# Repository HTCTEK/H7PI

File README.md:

# H7PI

## 量产版本历史
[v0.2](https://gitee.com/htctek/H7PI/tree/bf5159e9c3666d05ed6d5055ce2db61eb0288070) 特点：带8bits LCD接口    
[v1.0](https://gitee.com/htctek/H7PI/tree/e8b1aa18095ffa30b805f85c88335dfa602a2d0a) 特点：除了SD卡座，QSPI Flash引脚，SPI flash/psram引脚外，引出所有引脚，使用type-c接口，取消8bits LCD接口。

## 使用说明 / User Manual
中文：[使用说明](https://pinno.cc)

## 获取一个H7PI / Buy One
淘宝：[购买链接 / shop](https://item.taobao.com/item.htm?spm=a230r.1.14.18.71f35247DnH8yH&id=606908438435&ns=1&abbucket=14#detail)

## Platform
* [H7PI_Arduino](https://github.com/htctek/H7PI_Arduino) is for users who are used to develop arduino
* [H7PI_Samples](https://github.com/htctek/H7PI_Samples) is for users who are used to develop with MDK Keil, but also give an entry for arduino and support freeRTOS.

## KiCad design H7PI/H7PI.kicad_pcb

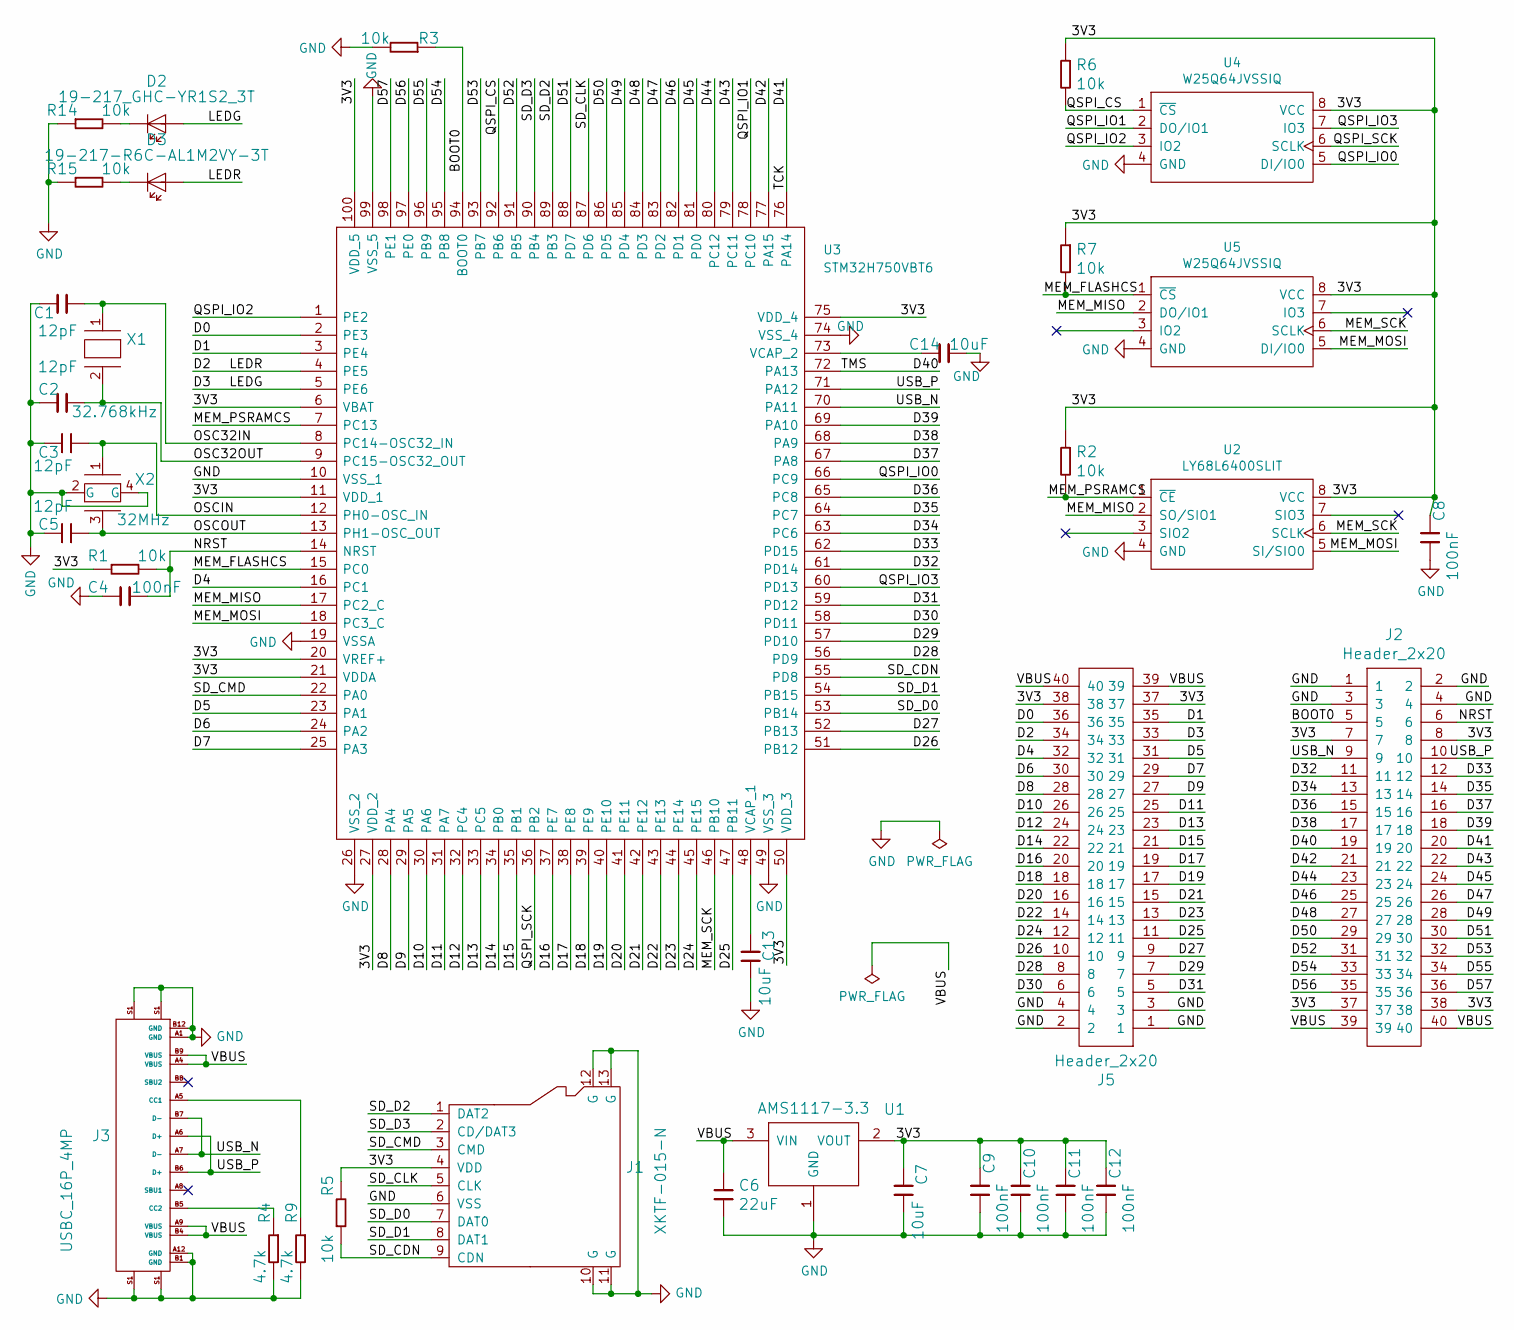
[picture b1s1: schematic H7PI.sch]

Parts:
C1, C2, C3, C5: 12pF; C_0402_1005Metric; PartNumber 0402CG120J500NT
C4, C8, C9, C10, C11, C12: 100nF; C_0402_1005Metric; PartNumber 0402B104K500NT
C6: 22uF; C_0805_2012Metric; PartNumber CL21A226MAQNNNE
C7, C13, C14: 10uF; C_0402_1005Metric; PartNumber 0402X106M6R3NT
D2: 19-217_GHC-YR1S2_3T; LED_0603_1608Metric; PartNumber 19-217/GHC-YR1S2/3T
D3: 19-217-R6C-AL1M2VY-3T; LED_0603_1608Metric; PartNumber 19-217/R6C-AL1M2VY/3T
J1: XKTF-015-N; Connector_MicroSD_TF_XKB_XKTF-015-N_14.75x17.5mm; PartNumber XKTF-015-N
J2, J5: Header_2x20; PinHeader_2x20_P2.54mm_Vertical
J3: USBC_16P_4MP; USB_C_Receptacle_Palconn_UTC16-G; PartNumber TYPE C连接器USB3.1系列母座端单排16P贴板有柱-5A大电流新ES
R1, R2, R3, R5, R6, R7, R14, R15: 10k; R_0402_1005Metric; PartNumber 0402WGF1002TCE
R4, R9: 4.7k; R_0402_1005Metric; PartNumber 0402WGF4701TCE
U1: AMS1117-3.3; SOT-223; PartNumber AMS1117-3.3
U2: LY68L6400SLIT; SOIC-8_3.9x4.9mm_P1.27mm; PartNumber LY68L6400SLIT
U3: STM32H750VBT6; LQFP-100_14x14mm_P0.5mm; PartNumber STM32H750VBT6
U4, U5: W25Q64JVSSIQ; SOIC-8_5.23x5.23mm_P1.27mm; PartNumber W25Q64JVSSIQ
X1: 32.768kHz; Crystal_SMD_EuroQuartz_EQ161-2Pin_3.2x1.5mm; PartNumber SMD31327681252090
X2: 32MHz; Crystal_SMD_2520-4Pin_2.5x2.0mm; PartNumber S2232000082060

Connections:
/3V3: C7.1, C8.2, C9.2, C10.2, C11.2, C12.2, J1.4 (VDD), J2.7, J2.8, J2.37, J2.38, J5.37, J5.38, R1.1, R2.1, R5.2, R6.1, R7.1, U1.2 (VOUT), U2.8 (VCC), U3.6 (VBAT), U3.11 (VDD_1), U3.20 (VREF+), U3.21 (VDDA), U3.27 (VDD_2), U3.50 (VDD_3), U3.75 (VDD_4), U3.100 (VDD_5), U4.8 (VCC), U5.8 (VCC)
/BOOT0: J2.5, R3.1, U3.94 (BOOT0)
/D0: J5.36, U3.2 (PE3)
/D1: J5.35, U3.3 (PE4)
/D2: D3.2, J5.34, U3.4 (PE5)
/D3: D2.2, J5.33, U3.5 (PE6)
/D4: J5.32, U3.16 (PC1)
/D5: J5.31, U3.23 (PA1)
/D6: J5.30, U3.24 (PA2)
/D7: J5.29, U3.25 (PA3)
/D8: J5.28, U3.28 (PA4)
/D9: J5.27, U3.29 (PA5)
/D10: J5.26, U3.30 (PA6)
/D11: J5.25, U3.31 (PA7)
/D12: J5.24, U3.32 (PC4)
/D13: J5.23, U3.33 (PC5)
/D14: J5.22, U3.34 (PB0)
/D15: J5.21, U3.35 (PB1)
/D16: J5.20, U3.37 (PE7)
/D17: J5.19, U3.38 (PE8)
/D18: J5.18, U3.39 (PE9)
/D19: J5.17, U3.40 (PE10)
/D20: J5.16, U3.41 (PE11)
/D21: J5.15, U3.42 (PE12)
/D22: J5.14, U3.43 (PE13)
/D23: J5.13, U3.44 (PE14)
/D24: J5.12, U3.45 (PE15)
/D25: J5.11, U3.47 (PB11)
/D26: J5.10, U3.51 (PB12)
/D27: J5.9, U3.52 (PB13)
/D28: J5.8, U3.56 (PD9)
/D29: J5.7, U3.57 (PD10)
/D30: J5.6, U3.58 (PD11)
/D31: J5.5, U3.59 (PD12)
/D32: J2.11, U3.61 (PD14)
/D33: J2.12, U3.62 (PD15)
/D34: J2.13, U3.63 (PC6)
/D35: J2.14, U3.64 (PC7)
/D36: J2.15, U3.65 (PC8)
/D37: J2.16, U3.67 (PA8)
/D38: J2.17, U3.68 (PA9)
/D39: J2.18, U3.69 (PA10)
/D40: J2.19, U3.72 (PA13)
/D41: J2.20, U3.76 (PA14)
/D42: J2.21, U3.77 (PA15)
/D43: J2.22, U3.79 (PC11)
/D44: J2.23, U3.80 (PC12)
/D45: J2.24, U3.81 (PD0)
/D46: J2.25, U3.82 (PD1)
/D47: J2.26, U3.83 (PD2)
/D48: J2.27, U3.84 (PD3)
/D49: J2.28, U3.85 (PD4)
/D50: J2.29, U3.86 (PD5)
/D51: J2.30, U3.88 (PD7)
/D52: J2.31, U3.91 (PB5)
/D53: J2.32, U3.93 (PB7)
/D54: J2.33, U3.95 (PB8)
/D55: J2.34, U3.96 (PB9)
/D56: J2.35, U3.97 (PE0)
/D57: J2.36, U3.98 (PE1)
/MEM_FLASHCS: R7.2, U3.15 (PC0), U5.1 (~CS)
/MEM_MISO: U2.2 (SO/SIO1), U3.17 (PC2_C), U5.2 (DO/IO1)
/MEM_MOSI: U2.5 (SI/SIO0), U3.18 (PC3_C), U5.5 (DI/IO0)
/MEM_PSRAMCS: R2.2, U2.1 (~CE), U3.7 (PC13)
/MEM_SCK: U2.6 (SCLK), U3.46 (PB10), U5.6 (SCLK)
/NRST: C4.1, J2.6, R1.2, U3.14 (NRST)
/OSC32IN: C1.2, U3.8 (PC14-OSC32_IN), X1.1
/OSC32OUT: C2.2, U3.9 (PC15-OSC32_OUT), X1.2
/OSCIN: C3.2, U3.12 (PH0-OSC_IN), X2.1
/OSCOUT: C5.2, U3.13 (PH1-OSC_OUT), X2.3
/QSPI_CS: R6.2, U3.92 (PB6), U4.1 (~CS)
/QSPI_IO0: U3.66 (PC9), U4.5 (DI/IO0)
/QSPI_IO1: U3.78 (PC10), U4.2 (DO/IO1)
/QSPI_IO2: U3.1 (PE2), U4.3 (IO2)
/QSPI_IO3: U3.60 (PD13), U4.7 (IO3)
/QSPI_SCK: U3.36 (PB2), U4.6 (SCLK)
/SD_CDN: J1.9 (CDN), R5.1, U3.55 (PD8)
/SD_CLK: J1.5 (CLK), U3.87 (PD6)
/SD_CMD: J1.3 (CMD), U3.22 (PA0)
/SD_D0: J1.7 (DAT0), U3.53 (PB14)
/SD_D1: J1.8 (DAT1), U3.54 (PB15)
/SD_D2: J1.1 (DAT2), U3.89 (PB3)
/SD_D3: J1.2 (CD/DAT3), U3.90 (PB4)
/USB_N: J2.9, J3.A7 (D-), J3.B7 (D-), U3.70 (PA11)
/USB_P: J2.10, J3.A6 (D+), J3.B6 (D+), U3.71 (PA12)
/VBUS: C6.1, J2.39, J2.40, J3.A4 (VBUS), J3.A9 (VBUS), J3.B4 (VBUS), J3.B9 (VBUS), J5.39, J5.40, U1.3 (VIN)
GND: C1.1, C2.1, C3.1, C4.2, C5.1, C6.2, C7.2, C8.1, C9.1, C10.1, C11.1, C12.1, C13.2, C14.2, J1.6 (VSS), J1.10 (G), J1.11 (G), J1.12 (G), J1.13 (G), J2.1, J2.2, J2.3, J2.4, J3.A1 (GND), J3.A12 (GND), J3.B1 (GND), J3.B12 (GND), J3.S1, J5.1, J5.2, J5.3, J5.4, R3.2, R4.2, R9.2, R14.1, R15.1, U1.1 (GND), U2.4 (GND), U3.10 (VSS_1), U3.19 (VSSA), U3.26 (VSS_2), U3.49 (VSS_3), U3.74 (VSS_4), U3.99 (VSS_5), U4.4 (GND), U5.4 (GND), X2.2 (G), X2.4 (G)
unnamed: C13.1, U3.48 (VCAP_1)
unnamed: C14.1, U3.73 (VCAP_2)
unnamed: D2.1, R14.2
unnamed: D3.1, R15.2
unnamed: J3.A5 (CC1), R9.1
unnamed: J3.B5 (CC2), R4.1

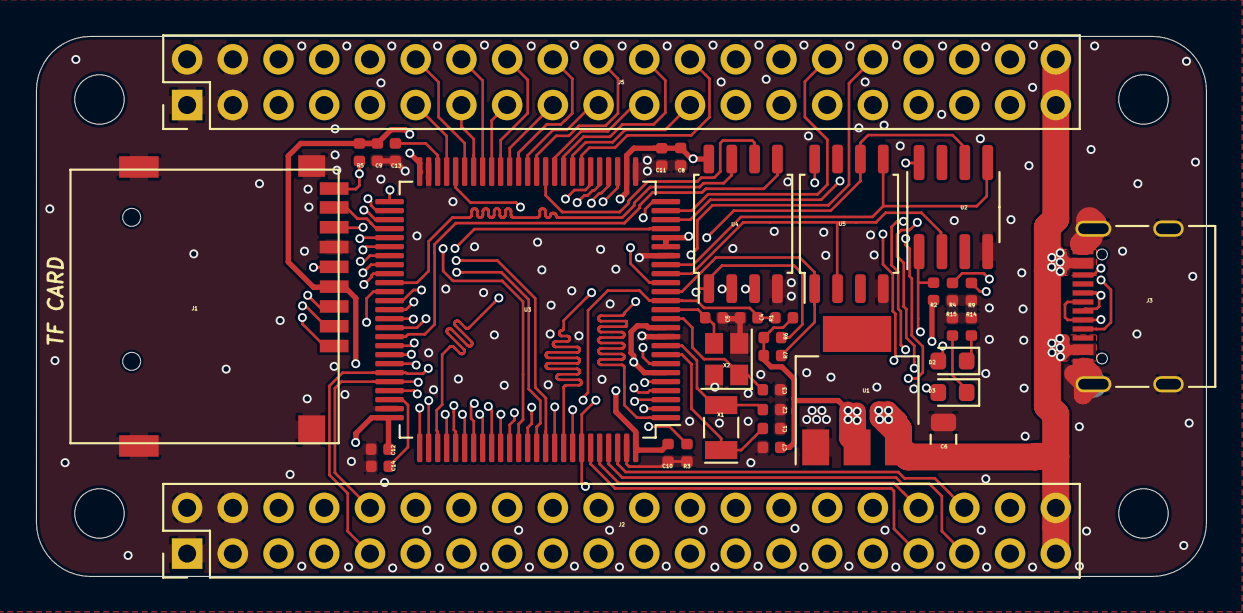
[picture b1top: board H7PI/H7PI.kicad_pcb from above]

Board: 4 copper layers, 65.0 x 30.0 mm, 37 parts (0 on the bottom side), 93 nets.

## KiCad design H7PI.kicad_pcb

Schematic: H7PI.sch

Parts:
C4, C8, C11, C12, C15, C16, C17, C18: 100nF; C_0402_1005Metric; PartNumber 0402B104K500NT
C5, C9: 1uF; C_0603_1608Metric; PartNumber 0603B105K500NT
C10: 100uF/10V; C_1210_3225Metric; PartNumber CL32A107MPVNNNE
C13, C14: 10uF; C_0402_1005Metric; PartNumber 0402X106M6R3NT
D1: 1N5819WS; D_SOD-323; PartNumber 1N5819WS
D2: 19-217_GHC-YR1S2_3T; LED_0603_1608Metric; PartNumber 19-217/GHC-YR1S2/3T
D3: 19-217-R6C-AL1M2VY-3T; LED_0603_1608Metric; PartNumber 19-217/R6C-AL1M2VY/3T
F1, F2: 0458002.DR; Fuse_1206_3216Metric; PartNumber 0458002.DR
J1: XKTF-015-N; Connector_MicroSD_TF_XKB_XKTF-015-N_14.75x17.5mm; PartNumber XKTF-015-N
J2: Header_2x10; PinHeader_2x10_P2.54mm_Vertical
J3, J6: microUSB; USB_Micro-B_Molex-105017-0001; PartNumber micro USB母座
J4: AFC07-S24ECA-00; Connector_FPC_JS_AFC07-S24ECA-00_1x24-1MP_P0.5mm_UpSideCont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; PartNumber AFC07-S24ECA-00
J5: Header_2x20; PinHeader_2x20_P2.54mm_Vertical
J7: Header_1x2; PinHeader_1x02_P1.27mm_Vertical
J8, J9: Header_1x1; TestPoint_Pad_D1.0mm
L1: CIGT201610LH2R2MNE; L_0805_2012Metric_Pad1.15x1.40mm_HandSolder; PartNumber CIGT201610LH2R2MNE
Q1: CJ2101; SOT-323_SC-70; PartNumber CJ2101
Q2: CJ2102; SOT-323_SC-70; PartNumber CJ2102
R1, R3, R5, R6, R7, R8, R9, R10, R13, R14, R15: 10k; R_0402_1005Metric; PartNumber 0402WGF1002TCE
R2: 33k; R_0402_1005Metric; PartNumber 0402WGF3302TCE
R4: 100k; R_0402_1005Metric; PartNumber 0402WGF1003TCE
R11: 4.7; R_0402_1005Metric; PartNumber 0402WGF470KTCE
R12: 1k; R_0402_1005Metric; PartNumber 0402WGF1001TCE
U2: MT1470; SOT-23-6; PartNumber MT1470
U3: STM32H750VBT6; LQFP-100_14x14mm_P0.5mm; PartNumber STM32H750VBT6
U4, U5: W25Q64JVSSIQ; SOIC-8_5.23x5.23mm_P1.27mm; PartNumber W25Q64JVSSIQ

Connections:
/3V3: C12.2, C15.2, C16.2, F1.2, J1.4 (VDD), J2.1, J4.1, J5.1, J5.17, Q1.2, R1.1, R5.2, R6.1, R7.1, R8.1, R9.1, R10.1, U3.6 (VBAT), U3.11 (VDD_1), U3.20 (VREF+), U3.21 (VDDA), U3.27 (VDD_2), U3.50 (VDD_3), U3.75 (VDD_4), U3.100 (VDD_5), U4.8 (VCC), U5.8 (VCC)
/BUZZER: R12.1, U3.59 (PD12)
/FLASH_CS: R7.2, U3.51 (PB12), U5.1 (~CS)
/FLASH_MISO: U3.17 (PC2_C), U5.2 (DO/IO1)
/FLASH_MOSI: U3.18 (PC3_C), U5.5 (DI/IO0)
/FLASH_SCK: U3.52 (PB13), U5.6 (SCLK)
/IO1: J2.3, U3.57 (PD10)
/IO2: J2.5, U3.60 (PD13)
/IO3: J2.7, U3.67 (PA8)
/IO4: J2.9, U3.72 (PA13)
/IO5: J2.11, U3.76 (PA14)
/IO6: J2.13, U3.77 (PA15)
/IO7: J2.15, U3.79 (PC11)
/IO8: J2.17, U3.80 (PC12)
/IO9: J2.18, U3.83 (PD2)
/IO10: J2.16, U3.84 (PD3)
/IO11: J2.14, U3.87 (PD6)
/IO12: J2.12, U3.88 (PD7)
/IO13: J2.10, U3.91 (PB5)
/IO14: J2.8, U3.96 (PB9)
/IO15: J2.6, U3.97 (PE0)
/IO16: J2.4, U3.98 (PE1)
/PI_CE0: J5.24, U3.41 (PE11)
/PI_CE1: J5.26, U3.45 (PE15)
/PI_GPIO0: J5.11, U3.2 (PE3)
/PI_GPIO1: J5.12, U3.3 (PE4)
/PI_GPIO2: J5.13, U3.4 (PE5)
/PI_GPIO3: J5.15, U3.5 (PE6)
/PI_GPIO4: J5.16, U3.7 (PC13)
/PI_GPIO5: J5.18, U3.15 (PC0)
/PI_GPIO6: J5.22, U3.24 (PA2)
/PI_GPIO7: J5.7, U3.25 (PA3)
/PI_GPIO21: J5.29, U3.28 (PA4)
/PI_GPIO22: J5.31, U3.29 (PA5)
/PI_GPIO23: J5.33, U3.30 (PA6)
/PI_GPIO24: J5.35, U3.31 (PA7)
/PI_GPIO25: J5.37, U3.32 (PC4)
/PI_GPIO26: J5.32, U3.33 (PC5)
/PI_GPIO27: J5.36, U3.34 (PB0)
/PI_GPIO28: J5.38, U3.35 (PB1)
/PI_GPIO29: J5.40, U3.56 (PD9)
/PI_MISO: J5.21, U3.43 (PE13)
/PI_MOSI: J5.19, U3.44 (PE14)
/PI_RXD: J5.10, U3.69 (PA10)
/PI_SCK: J5.23, U3.42 (PE12)
/PI_SCL0: J5.28, U3.95 (PB8)
/PI_SCL1: J5.5, U3.46 (PB10)
/PI_SDA0: J5.27, U3.93 (PB7)
/PI_SDA1: J5.3, U3.47 (PB11)
/PI_TXD: J5.8, U3.68 (PA9)
/QSPI_CS: R6.2, U3.92 (PB6), U4.1 (~CS)
/QSPI_IO0: U3.66 (PC9), U4.5 (DI/IO0)
/QSPI_IO1: U3.78 (PC10), U4.2 (DO/IO1)
/QSPI_IO2: U3.1 (PE2), U4.3 (IO2)
/QSPI_IO3: U3.23 (PA1), U4.7 (IO3)
/QSPI_SCK: U3.36 (PB2), U4.6 (SCLK)
/TFT_BL: Q1.1, R10.2, U3.63 (PC6)
/TFT_CS: J4.5, R9.2, U3.64 (PC7)
/TFT_DB8: J4.17, U3.61 (PD14)
/TFT_DB9: J4.18, U3.62 (PD15)
/TFT_DB10: J4.19, U3.81 (PD0)
/TFT_DB11: J4.20, U3.82 (PD1)
/TFT_DB12: J4.21, U3.37 (PE7)
/TFT_DB13: J4.22, U3.38 (PE8)
/TFT_DB14: J4.23, U3.39 (PE9)
/TFT_DB15: J4.24, U3.40 (PE10)
/TFT_RD: J4.8, U3.85 (PD4)
/TFT_RS: J4.6, U3.58 (PD11)
/TFT_RST: C17.2, J4.4, R8.2, U3.65 (PC8)
/TFT_WR: J4.7, U3.86 (PD5)
/TF_CDN: J1.9 (CDN), R5.1, U3.55 (PD8)
/TF_CLK: J1.5 (CLK), U3.16 (PC1)
/TF_CMD: J1.3 (CMD), U3.22 (PA0)
/TF_DATA0: J1.7 (DAT0), U3.53 (PB14)
/TF_DATA1: J1.8 (DAT1), U3.54 (PB15)
/TF_DATA2: J1.1 (DAT2), U3.89 (PB3)
/TF_DATA3: J1.2 (CD/DAT3), U3.90 (PB4)
/USB_N: J3.2, J6.2, U3.70 (PA11); also elsewhere on the board
/USB_P: J3.3, J6.3, U3.71 (PA12); also elsewhere on the board
/VBUS: C5.1, C8.2, D1.1, F2.1, J2.2, J5.2, J5.4, J7.1, U2.3; also elsewhere on the board
GND: C4.2, C5.2, C8.1, C10.2, C11.1, C12.1, C13.2, C14.2, C15.1, C16.1, C17.1, C18.2, J1.6 (VSS), J1.10 (G), J1.11 (G), J1.12 (G), J1.13 (G), J2.19, J2.20, J3.5, J3.6, J4.2, J4.9, J4.10, J4.11, J4.12, J4.13, J4.14, J4.15, J4.16, J4.MP, J5.6, J5.9, J5.14, J5.20, J5.25, J5.30, J5.34, J5.39, J6.5, J6.6, J8.1, J9.1, Q2.2, R2.2, R3.1, R13.2, R14.1, R15.1, U2.1, U3.10 (VSS_1), U3.19 (VSSA), U3.26 (VSS_2), U3.49 (VSS_3), U3.74 (VSS_4), U3.99 (VSS_5), U4.4 (GND), U5.4 (GND); also elsewhere on the board
unnamed: C4.1, R1.2, U3.14 (NRST)
unnamed: C9.1, U2.6
unnamed: C9.2, L1.1, U2.2
unnamed: C10.1, C11.2, F1.1, L1.2, R4.2
unnamed: C13.1, U3.48 (VCAP_1)
unnamed: C14.1, U3.73 (VCAP_2)
unnamed: C18.1, D1.2, J7.2, Q2.3
unnamed: D2.1, R14.2
unnamed: D2.2, U3.8 (PC14-OSC32_IN)
unnamed: D3.1, R15.2
unnamed: D3.2, U3.9 (PC15-OSC32_OUT)
unnamed: F2.2, J3.1, J6.1
unnamed: J4.3, R11.2
unnamed: Q1.3, R11.1
unnamed: Q2.1, R12.2, R13.1
unnamed: R2.1, R4.1, U2.4
unnamed: R3.2, U3.94 (BOOT0)
unnamed 98: U2.5; also elsewhere on the board

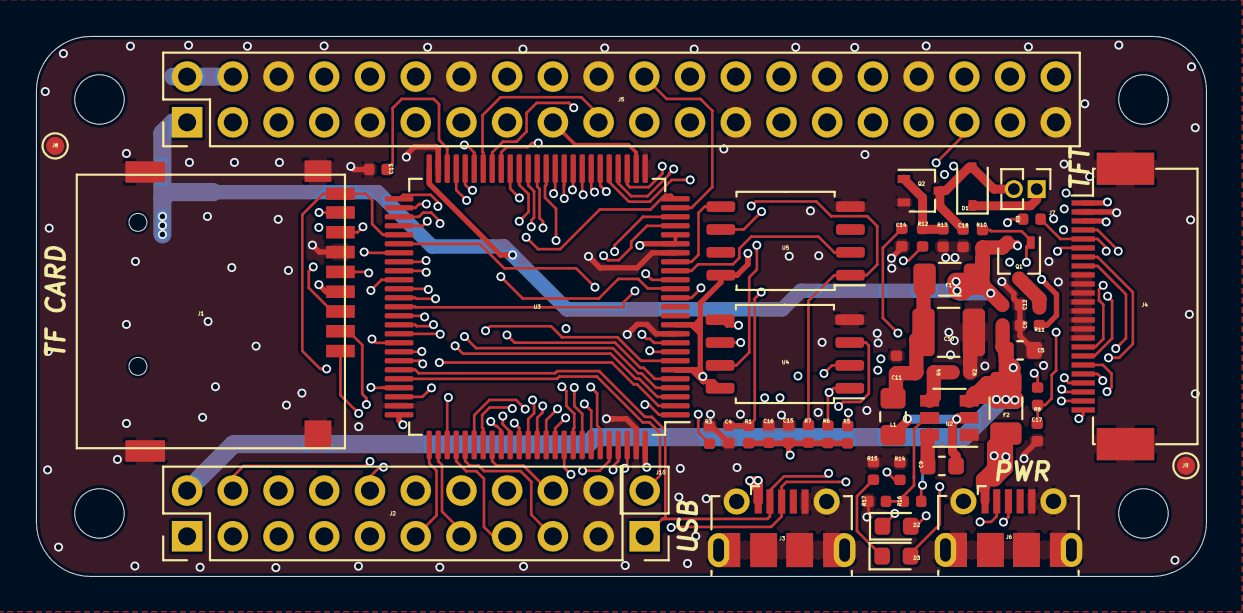
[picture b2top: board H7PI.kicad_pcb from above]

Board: 4 copper layers, 65.0 x 30.0 mm, 52 parts (0 on the bottom side), 99 nets.

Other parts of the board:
J10: DNP; PinHeader_1x02_P2.54mm_Vertical
R16: 100k; R_0402_1005Metric
R17: 33k; R_0402_1005Metric

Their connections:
/USB_N: J10.1; also elsewhere on the board
/USB_P: J10.2; also elsewhere on the board
/VBUS: R16.1; also elsewhere on the board
GND: R17.2; also elsewhere on the board
unnamed 98: R16.2, R17.1; also elsewhere on the board

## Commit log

2019-10-29 0.2版本，经试产可用于量产
2019-12-24 add README.md.
2019-12-24 更新了图纸的信息
2019-12-24 更新readme，增加中文简要说明
2019-12-24 增加英文首页readme add english readme
2019-12-28 v0.3 1. 增加电压支持到12V 2. 增加双USB口通信（不能同时用） 3. 增加USB通孔，用于底板扩展，正常为DNP状态
2020-01-09 update license to BSD
2020-01-10 update readme and pic
2020-01-10 update readme and pic Signed-off-by: fuhua-chen <fuhua-chen@outlook.com>
2020-01-10 update pic
2020-01-16 v0.4 add pin info to bottom silk change pin name to Dx,Ax.
2020-03-20 v1.0开发起点 1. 不再使用树莓派外型 2. 使用Type C USB接口 3. 不再板载LCD接口 4. 板载PSRAM,QSPI FLASH,SPI FLASH 5. 保留TF卡接口
2020-03-20 v1.0第一次推送，待打样 Signed-off-by: fuhua-chen <fuhua-chen@outlook.com>
2020-04-09 update README.md.
2020-04-13 更新晶振配置 Signed-off-by: fuhua.chen <fuhua-chen@outlook.com>
